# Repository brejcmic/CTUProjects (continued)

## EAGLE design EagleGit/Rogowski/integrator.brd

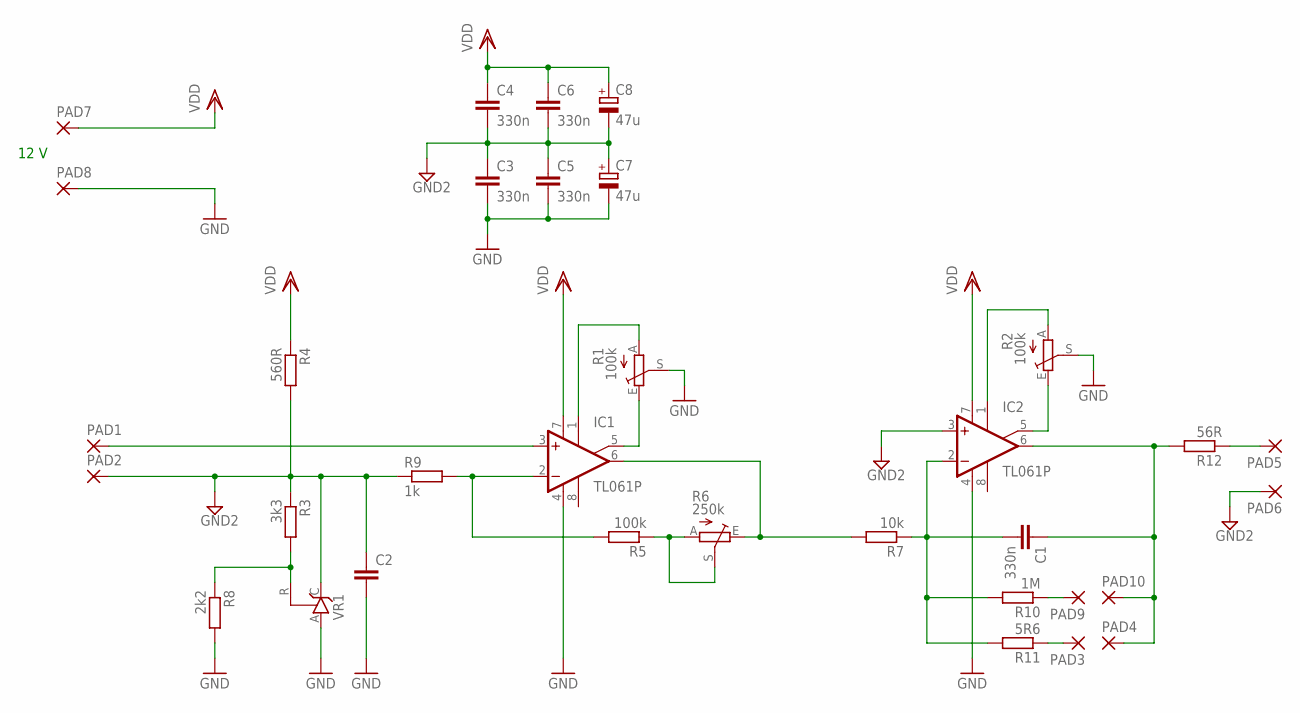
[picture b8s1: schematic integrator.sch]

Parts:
C1, C3, C4, C5, C6: 330n; C050-035X075
C2: C-EU050-035X075; C050-035X075
C7, C8: 47u; E2,5-7
IC1, IC2: TL061P; DIL08
PAD1, PAD2, PAD3, PAD4, PAD5, PAD6, PAD7, PAD8, PAD9, PAD10: 3,81/1,4
R1, R2: 100k; LI10
R3: 3k3; 0207/12
R4: 560R; 0207/12
R5: 100k; 0207/12
R6: 250k; LI10
R7: 10k; 0207/12
R8: 2k2; 0207/12
R9: 1k; 0207/12
R10: 1M; 0207/12
R11: 5R6; 0207/12
R12: 56R; 0207/12
VR1: TL431CLP; TO92-CLP

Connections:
GND: C2.2, C3.2, C5.2, C7.-, IC1.4 (V-), IC2.4 (V-), PAD8.1, R1.S, R2.S, R8.2, VR1.A
GND2: C2.1, C3.1, C4.2, C5.1, C6.2, C7.+, C8.-, IC2.3 (+IN), PAD2.1, PAD6.1, R3.1, R4.2, R9.1, VR1.C
unnamed: IC1.5 (ON2), R1.E
unnamed: IC1.1 (ON1), R1.A
unnamed: IC2.5 (ON2), R2.E
unnamed: IC2.1 (ON1), R2.A
unnamed: IC1.2 (-IN), R5.2, R9.2
unnamed: R5.1, R6.A, R6.S
unnamed: IC1.6 (OUT), R6.E, R7.2
unnamed: C1.2, IC2.2 (-IN), R7.1, R10.2, R11.2
unnamed: R3.2, R8.1, VR1.R
unnamed: PAD9.1, R10.1
unnamed: IC1.3 (+IN), PAD1.1
unnamed: PAD3.1, R11.1
unnamed: PAD5.1, R12.1
OUT: C1.1, IC2.6 (OUT), PAD4.1, PAD10.1, R12.2
VDD: C4.1, C6.1, C8.+, IC1.7 (V+), IC2.7 (V+), PAD7.1, R4.1

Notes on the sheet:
12 V

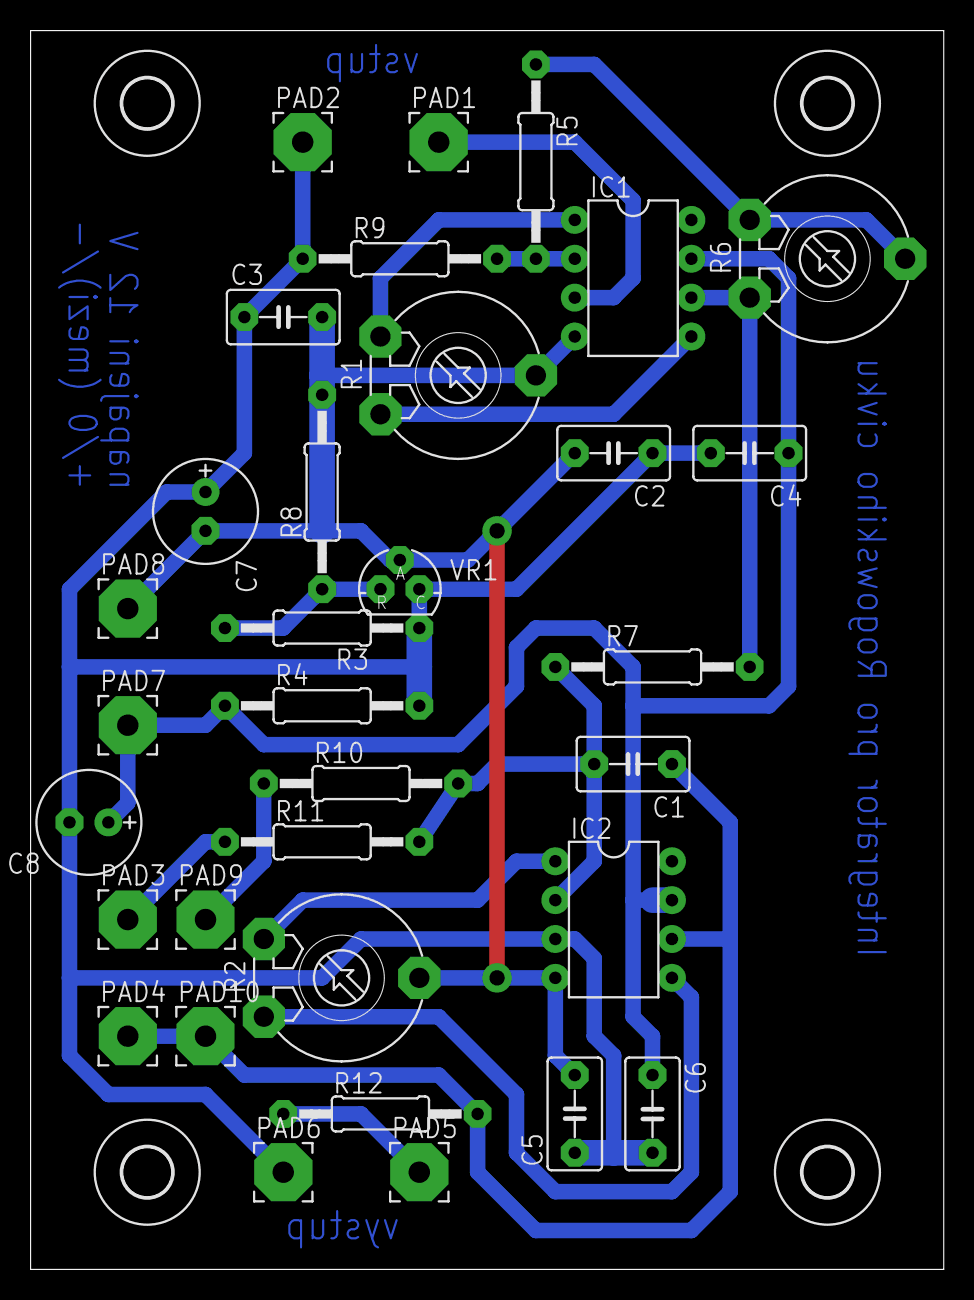
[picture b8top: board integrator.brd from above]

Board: 2 copper layers, 59.7 x 81.0 mm, 37 parts (0 on the bottom side), 17 nets.

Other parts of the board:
U$1, U$2, U$3, U$4: 3,2

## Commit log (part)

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2015-02-13 Zakladni zdrojove soubory pro konferenci EPE2015
2015-02-13 Vymazani nepotrebnych souboru z repozitare, priprava na gitignore
2015-02-13 Doplneni obrazku do gitignore, okotovany obrazek chodniku, uprava zakladnich dokumentu pro spravne cteni cestiny, sazbu rovnic a obrazku
2015-02-16 Opravena chyba v README.txt
2015-02-16 Z gitignore jsou odebrany povolena pdf
2015-02-17 Započatí psaní na souboru sexRoadLightingDesign.
2015-02-17 Doplneny vysledky vypoctu jednotlivych svitidel do clanku
2015-02-17 Opravena chyba v gitignore pro soubory txt
2015-02-17 Vymazan soubor closet.tex a doplnen do dokumentu soubor secRoadLightingDesign
2015-02-17 Priprava algoritmu na vypocet osvetleni mimo komunikaci. Odstranena vzdalenost sloupu ze zadani algoritmu.
2015-02-17 Dopsán vztah pro udržovací činitel.
2015-02-17 Odstavec norem s dopočítaným udržovacím činitelem.
2015-02-18 Do hlavního souboru přidány citace norem. Do odtsavce s normama přidán pokus o referenci na citaci.
2015-02-18 Zmenen seznam autoru
2015-02-18 Predelan obrazek chodniku
2015-02-18 Opraven zapis url
2015-02-18 Hotova kapitola o fitness a elitismu, zapsany vysledky ze svitidel B1-B4
2015-02-19 Pridana svitidla 50 W
2015-02-19 Napsan zacatek kapitoly o vysledcich genetickeho algoritmu, pridany vysledky svitidla C1, opraveny drobne chyby v textu, doplnena citace literatury
2015-02-19 Dokoncena tabulka se svitidly A1-C4
2015-02-19 Doplneny obrazky ze simulace, pouzit balik subfig.sty
2015-02-19 Kapitola Pelanice započata.
2015-02-19 Obrázek Atose.
2015-02-19 C-gamma B-beta popis.
2015-02-20 Dopsán odstavec o svítidle.
2015-02-20 Smazana 50 W svitidla, presunut popis dialuxu do kapitoly example of the solution
2015-02-20 Dopisování kapitoly Results.
2015-02-20 Vraceno illuminance a dopsan abstract
2015-02-20 Oprava abstraktu.
2015-02-21 Odeslana verze clanku
2015-02-24 Zdrojove soubory pro konferenci Light Svetlo 2015
2015-02-26 Zakladni vzor pro clanek na konferenci Light Svetlo 2015
2015-03-03 Light Svetlo 2015 abstrakt
2015-03-04 Zaklad algoritmu pro krivku svitivosti, zatim moc dobre nechodi
2015-03-19 Overeno, ze algoritmus adaptace krivky svitivosti chodi pro jedno svitidlo bez odrazu sten.
2015-03-19 Zmenen vypocet fitnes u GA krivky, opravena chyba ve vypoctu svitivosti. Program funguje, ale moznost volby krivky svitivosti je znacne omezena.
2015-03-24 Dodelana osvetlenost na srovnavaci rovine. Fitness funkce ma obcas tendenci klesnout = v pridanem kodu je nekde chyba.
2015-03-24 Doplnena zavislost na I0 a stredni hodnote. Upraven vypocet svitivosti.
2015-03-31 vracena nulova rovina, upravena fitness, upraveno vykreslovani grafu osvetleni
2015-04-01 Algoritmus pozic svitidel byl upraven do podoby algoritmu krivky (srovnavaci rovina atd.) a zaroven byla zmenena fitnessfunkce. Spatna konvergence algoritmu. Je treba vyzkouset turnajovy vyber rodicu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
2015-04-01 opravena chyba v mutaci, ve svitidelch je turnajovy vyber rodicu
2015-04-02 New parallel file added. Will work ion this file in the future and somehow someone will have to combine those 2 files later
2015-04-02 Introduction slighty updated...
2015-04-04 Vytvorena osnova clanku a udelana kapitola Parent selection.
2015-04-06 Zmena fitness funkce
2015-04-07 Writing about CSN EN 12464 requirements.
2015-04-07 Určeno string appears... deleted.
2015-04-07 Zpráva pro Majkla...
2015-04-07 Standard intro edit.
2015-04-09 Calculating illuminances of the reference plane chapter has been created.
2015-04-09 Doplnena stredova symetrie do fitness funkce. Momentalni nastaveni svitivosti by melo byt prvni do clanku.
2015-04-10 GASVP_test1: Vysledek do clanku
2015-04-11 Multiple diffuse reflection explaining image made better.
2015-04-11 Some more about multiple reflections added.
2015-04-12 Dodelana sekce s nastavenim GA a Survival selection
2015-04-13 Zakladni popis v kapitolach s fitness funkcemi a definicemi DNA
2015-04-13 Multiple reflections description.
2015-04-13 Vysledky vlozeny do clanku
2015-04-13 How to calculate illuminance of the reference plane...
2015-04-13 Slouceny moje zmeny a zmeny rudy.
2015-04-13 Znovu sloučeny moje a Rudovy změny
2015-04-13 Reflections edited.
2015-04-13 Doplnen text s vysledky mereni.
2015-04-14 oprava zahlavy tabulky
2015-04-14 Upraveno formatovani clanku
2015-04-14 Smrsknuti clanku na 5 stranek
2015-04-14 Casopis s impact factorem - informace
2015-04-15 Pridany styly casopisu
2015-04-16 Pokus o upravu manuscriptu tak, aby format odpovidal pouziti v LibreOffice
2015-04-16 Oprava stylu v LightSvetlo2015RTF.rtf
2015-05-05 Upraven program pro terarko, pripraveny registry pro I2C a UART
2015-05-14 Footnote edit, acknowledgments, finetuning.
2015-05-31 Provedeny upravy clanku - zmena citaci, odsazeni autoru od nadpisu a vymazani acknoledgements
2015-06-03 Opravena prezentace na Temesvar. Pridany informace o CNR a harmonickem kondicioneru.
2015-07-23 Pomoci instrukce trap bylo odzkouseno prepinani tasku. V simulatoru mi nebezi citac, takze jsem nebyl schopen vyskouset volani scheduleru z preruseni citace. Do inicializace stacku bylo potreba prida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
2015-07-24 Prace na I2C, je treba rozmyslet, jak se bude nacitat cas a zda se to nebude odehravat v nekterem vlakne.
2015-08-11 mensi upravy algoritmu
2015-08-12 Oprava chyb ve funkcich vypoctu osvetleni - spatny vypocet pruvodice Funkce pouzity v hlavnim skriptu a odzkouseny.
2015-08-19 Terarko: - pridadana dokumentace k procesoru a modulu bluetooth - upravena funkce kernelu = scheduler tak, aby mazala vlajku preruseni - inicializace vlaken presunuta do Peripheral.c
    - odzkouseno, vlakna chodi spravne.
2015-08-20 Terarko: - chyba na ridici desce, byly prohozeny TX a RX privody k bluetooth modulu.
2015-08-20 Terarko: - do cesty Rx, CTS pridany 1k rezistory
2015-08-21 Terarko: - pridana dokumentace COSMIC
2015-08-25 LR&T: -priprava podprogramu svitidla C-Gama, neni dodelano cteni z tabulky svitivosti.
2015-08-27 Terarko: - zvetseny prostor pro diody
2015-08-28 Terarko: -snaha o implementaci i2c, pouze uložení rozdělané práce
2015-08-30 Drobna uprava Peripheral.c
2015-08-31 Terarko: I2C chodi, ale neni jasne proc.
2015-09-01 Terarko: - funkcni nastavovani casu RTC
2015-09-01 Terarko: -pridany nektere funkce jako rtc update apod. -vsechny tabulatory nahrazeny dvema mezerama
2015-09-03 LR&T: - opraven vyznam vektoru vax a vrd
2015-09-03 Terarko: -rozpracovana uprava podprogramu I2C
2015-09-04 Terarko: - pridany symbolicke konstanty pro UART - pridano hlidani chyb v UART
2015-09-04 Terarko: -na DPS pridan napajeci konektor -na DPS pridan konektor SPI -opraveny vsechny cesty
2015-09-11 LR&T: -script pripraven pro simulace
2015-09-11 LR&T: - zarazena svitidla pro testovani algoritmu
2015-09-18 LR&T: -do fitness funkce dodelana podminka symetrie -vzgenerovano nekolik vysledku, ale jeste pred uvazovanim symetrie
2015-09-25 LR&T: - vysledky s uvazovanim symetrie - bude treba udelat jeste jedno nove testovani pro symetricky rozmistena svitidla. Tj. novy navrh DNA.
2015-10-09 VES: Pridan pripravek pro mereni tranzistoru.
2015-10-26 Zesilovac pro merici transformator proudu.
2015-11-06 Vytvorena cela pro Rogowskiho civku a dodelan budic LED
2016-01-08 PCB: -desky pro projekt termoclanky
2016-01-14 Added poster for Light 2015 and EPE2015.
2016-01-15 Nova koncepce koncoveho zesilovace podle Papeze. Je treba dodelat totez pro ostatni vstupy.
2016-01-17 Termoclanky: Hotovy navrh dps zesilovacu.
2016-01-18 Termistory: - predelany zakoncovaci rezistory na vetsi vykony - rozsireny cesty - finalni verze DPS
2016-01-19 EPE2016 a LR&T: - dokoncen GA s rastrem svitidel. - dva typy symetrii: stredova, osova (ted nastavena) - vse se zda ze chodi
2016-01-20 EPE2016: - zakladni osnova
2016-01-21 notes
2016-01-22 EPE2016: -zacatek kapitoly o symetrii
2016-01-23 EPE2016: Napsana kapitola o symetrii a DNA
2016-01-26 Started to write section I.
2016-01-27 EPE2016: - zadana nova svitidla - stale je zde rozdil mezi nasimi vysledky a vysledky ve Wills
2016-01-28 Section I started, Section II started
2016-02-02 Akvarko: - verze dps do bakalarky, ktera byla zaslana a byla v ni objevena minimalne jedna chyba.
2016-02-02 Lambertian reflectance added, etc.
2016-02-02 Redrawn image deleted.
2016-02-03 Do gitignore pridany Matlab soubory *.fig.
2016-02-03 EPE2016: Finalni verze vysledku. Doporucuji v clanku pouzit ty, kde jsou svitidla orientovany do smeru V010.
2016-02-05 Termoclanky: -finalni upravy DPS pred vyrobou
2016-02-08 EPE2016: - dotvoreny kapitoly s vysledky a chovanim algoritmu x zbyva dodelat abstrakt a zaver
2016-02-08 EPE2016: - dopsany zaver
2016-02-09 Nothing important.
2016-02-09 Section I and II read and corrected.
2016-02-09 EPE2016: - prvni opravne cteni kapitol o GA
2016-02-11 EPE2016: - preorganizovani prvku v clanku, aby dosahl rozumneho vizualniho vzhledu.
2016-02-18 Akvarko: - zakladni navrh DPS a rozmisteni soucastek.
2016-02-19 Akvarko2: - navržené DPS. x bylo by vhodné doplnit filtrační kondenzátory k napájecím vstupům.
2016-02-23 LR&T: - zaklad manuskriptu
2016-04-07 EPE2016: - zmeneno DNA na genotype - pridana specifikace zarizeni, na kterem algoritmus bezel
2016-04-07 EPE2016 - Copyright file added.
2016-04-23 Opravena chyba v tex souboru manuscriptu
2016-04-26 SAGE guide pdf and Vancouver reference style pdf added.
2016-04-26 Started to overwrite Introduction section. Guideline documents added.
2016-04-28 LR&T: -pridelany kapitoly -napsan kousek k Design Requirements
2016-04-28 Changes made to EPE2016 due to requirements of mistr John Shoemaker.
2016-04-30 LR&T: - bez pdf souboru v repozitari
2016-04-30 LR&T: -pridana cast ke GA -pridana cast k pozadavkum navrhu -doplnena literatura
2016-05-01 Minor changes to secQuality
2016-05-03 Section 'Quality' has been finished.
2016-05-05 Affiliation editing started.
2016-05-05 LR&T: - zakladni verze textu GA Intorduction - zakladni verze textu Design Requirements
2016-05-05 LR&T: - opraveny chyby v zapisu vysledku GA - pridana permutace do GA - vygenerovany vysledky pro 3 typy fitness funkce, vse pro centralni symetrii
2016-05-07 LR&T: - zaklad kapitoly Model Room
2016-05-12 LR&T: - vzgenerovanz vzsledky pro obe symetrie
2016-05-18 EPE2016: - pridana prezentace
2016-05-26 LR&T: - polovina kapitoly o fitness funkci hotova
2016-05-28 LR&T: - pridana dalsi sekce o vystupech algorytmu
2016-05-29 LR&T: - doplnen text k "Settings" v kapitole "GA Outputs"
2016-05-31 Finalizing of project EPE2016.
2016-05-31 LR&T: - upravena fitness funkce do shodz s clankem
2016-06-01 LR&T: - pregenerovane vysledky pro centralni symetrii a rouyne nastaveni fitness funkce: a= 0.5, a= 0, a= 1;
2016-06-03 LR&T: - hotovy koncept clanku - vygenerovany nove vysledky - smazany vysledky navic - kapitola Problemy nahrayena kapitolou Zaver
2016-06-18 LR&T: - vyhozen popis stare ucelove funkce - upraveno zobrazeni dokumentu zmenou velikosti tabulek apod. - pridan zaver
2016-06-22 LR&T: - opraven obrazek modeloveho pokoje
2016-06-22 LR&T: - opraven zapis rovnice s cilovym pomerem sledovanych parametru - opraven vzhled dokumentu do cilove podoby
2016-07-04 Termoclanky: - koncept pcb
2016-07-07 Termoclanky + manuskript: - priprava do rtf
2016-07-13 zaloha quanti2
2016-09-06 LumenV4 2016 almost finished.
2016-09-08 LumenV4 2016 poster done
2016-09-13 LumenV4 poster finalized.
2016-09-27 DPS: - pocatecni navrh nabijecky x nedodelano
2016-10-25 Rewriting TEX SAGE manuscript into Word started. Chapters "Introduction" and "Lighting System Quality Evaluation" done.
2017-01-15 Zacatek prezentace EMC
2017-02-04 zakon 90/ 2016
2017-02-08 EMC: - doplněny dva slajdy s NV 173/ 1997 Sb.
2017-02-09 Zakon 90
2017-02-13 Pridana osnova Continental
2017-03-10 EMC: - dokresleny obrazky a pridany dokumenty COI
2017-04-21 EMC: - screen shoty DPS
2017-04-23 EMC: - grafy pro soucastky
2017-04-24 simulace 4
2017-04-24 EMC: - dalsi slajdy
2017-04-25 EMC: - opraveno dle konzultace
2017-04-25 EMC: - zkresleni signalu na vedeni
2017-04-25 EMC - obrazek vedeni
2017-04-25 EMC: - pevne instalace
2017-04-25 EMC: - temer hotovo
2017-04-25 EMC: -castecne hotovo
2017-04-27 LR&T paper intro reworked in doc file.
2017-05-11 LR&T paper: First rewrite done to chapter Conclusion.
2017-05-18 Reference numbers chnaged to superscript.
2017-06-07 Submission help document added.
2017-06-14 Title of LR&T paper changed.
